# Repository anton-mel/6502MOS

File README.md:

# Simplified 6502 MOS

A simplified version of the MOS 6502 8-bit microprocessor with only a subset of its instructions. The 6502 is a classic CPU that powered some of the popular early systems such as the Apple II and NES.

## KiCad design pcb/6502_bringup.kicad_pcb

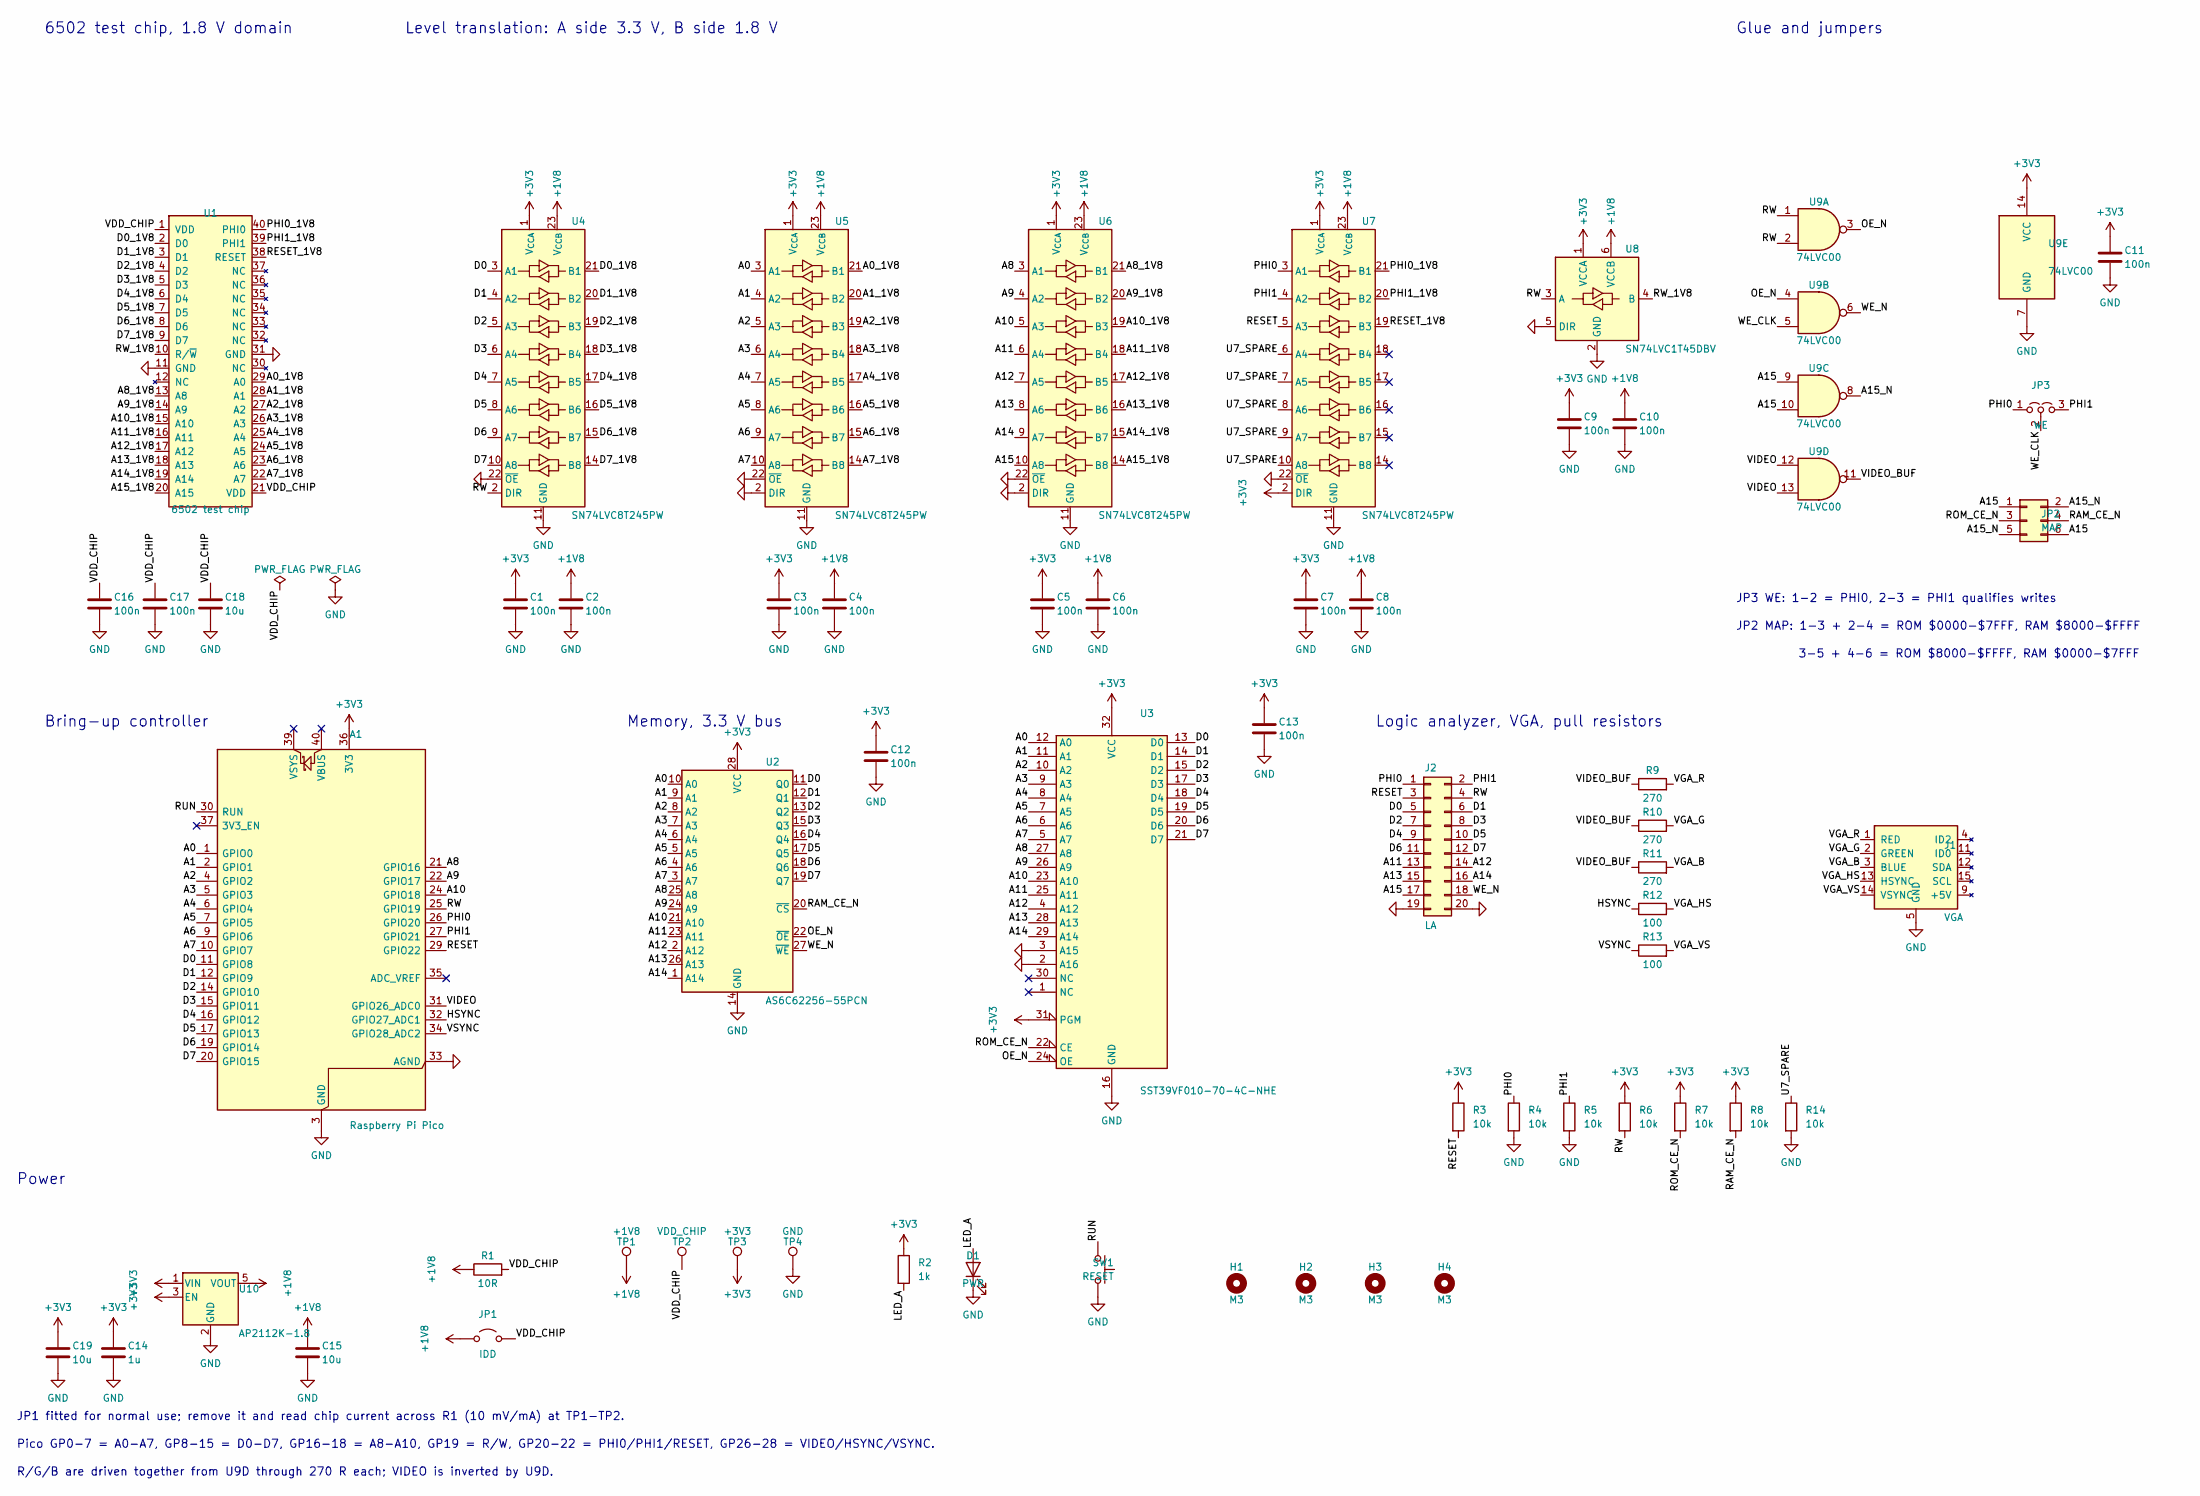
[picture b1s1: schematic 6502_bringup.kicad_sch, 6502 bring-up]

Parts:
A1: Raspberry Pi Pico; RaspberryPi_Pico_Common_THT; MPN SC0915
C1, C2, C3, C4, C5, C6, C7, C8, C9, C10, C11, C12, C13, C16, C17: 100n; C_0805_2012Metric
C14: 1u; C_0805_2012Metric
C15, C18, C19: 10u; C_0805_2012Metric
D1: PWR; LED_0805_2012Metric
H1, H2, H3, H4: M3; MountingHole_3.2mm_M3
J1: VGA; DSUB-15-HD_Socket_Horizontal_P2.29x1.90mm_EdgePinOffset3.03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
J2: LA; PinHeader_2x10_P2.54mm_Vertical
JP1: IDD; PinHeader_1x02_P2.54mm_Vertical
JP2: MAP; PinHeader_2x03_P2.54mm_Vertical
JP3: WE; PinHeader_1x03_P2.54mm_Vertical
R1: 10R; R_0805_2012Metric
R2: 1k; R_0805_2012Metric
R3, R4, R5, R6, R7, R8, R14: 10k; R_0805_2012Metric
R9, R10, R11: 270; R_0805_2012Metric
R12, R13: 100; R_0805_2012Metric
SW1: RESET; SW_PUSH_6mm
TP1: +1V8; TestPoint_Loop_D2.50mm_Drill1.0mm; MPN Keystone 5000
TP2: VDD_CHIP; TestPoint_Loop_D2.50mm_Drill1.0mm; MPN Keystone 5000
TP3: +3V3; TestPoint_Loop_D2.50mm_Drill1.0mm; MPN Keystone 5000
TP4: GND; TestPoint_Loop_D2.50mm_Drill1.0mm; MPN Keystone 5000
U1: 6502 test chip; ZIF-40_W15.24mm_3M_240-1280; MPN 3M 240-1280-00-0602J (socket)
U2: AS6C62256-55PCN; DIP-28_W15.24mm; MPN AS6C62256-55PCN
U3: SST39VF010-70-4C-NHE; PLCC-32_THT-Socket; MPN SST39VF010-70-4C-NHE
U4, U5, U6, U7: SN74LVC8T245PW; TSSOP-24_4.4x7.8mm_P0.65mm; MPN SN74LVC8T245PWR
U8: SN74LVC1T45DBV; SOT-23-6; MPN SN74LVC1T45DBVR
U9: 74LVC00; SOIC-14_3.9x8.7mm_P1.27mm; MPN SN74LVC00AD
U10: AP2112K-1.8; SOT-23-5; MPN AP2112K-1.8TRG1

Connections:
+1V8: C2.1, C4.1, C6.1, C8.1, C10.1, C15.1, JP1.1 (A), R1.1, TP1.1, U4.23 (V_{CCB}), U4.24 (V_{CCB}), U5.23 (V_{CCB}), U5.24 (V_{CCB}), U6.23 (V_{CCB}), U6.24 (V_{CCB}), U7.23 (V_{CCB}), U7.24 (V_{CCB}), U8.6 (VCCB), U10.5 (VOUT)
+3V3: A1.36 (3V3), C1.1, C3.1, C5.1, C7.1, C9.1, C11.1, C12.1, C13.1, C14.1, C19.1, R2.1, R3.1, R6.1, R7.1, R8.1, TP3.1, U2.28 (VCC), U3.31 (PGM), U3.32 (VCC), U4.1 (V_{CCA}), U5.1 (V_{CCA}), U6.1 (V_{CCA}), U7.1 (V_{CCA}), U7.2 (DIR), U8.1 (VCCA), U9.14 (VCC), U10.1 (VIN), U10.3 (EN)
/A0: A1.1 (GPIO0), U2.10 (A0), U3.12 (A0), U5.3 (A1)
/A0_1V8: U1.29 (A0), U5.21 (B1)
/A1: A1.2 (GPIO1), U2.9 (A1), U3.11 (A1), U5.4 (A2)
/A1_1V8: U1.28 (A1), U5.20 (B2)
/A2: A1.4 (GPIO2), U2.8 (A2), U3.10 (A2), U5.5 (A3)
/A2_1V8: U1.27 (A2), U5.19 (B3)
/A3: A1.5 (GPIO3), U2.7 (A3), U3.9 (A3), U5.6 (A4)
/A3_1V8: U1.26 (A3), U5.18 (B4)
/A4: A1.6 (GPIO4), U2.6 (A4), U3.8 (A4), U5.7 (A5)
/A4_1V8: U1.25 (A4), U5.17 (B5)
/A5: A1.7 (GPIO5), U2.5 (A5), U3.7 (A5), U5.8 (A6)
/A5_1V8: U1.24 (A5), U5.16 (B6)
/A6: A1.9 (GPIO6), U2.4 (A6), U3.6 (A6), U5.9 (A7)
/A6_1V8: U1.23 (A6), U5.15 (B7)
/A7: A1.10 (GPIO7), U2.3 (A7), U3.5 (A7), U5.10 (A8)
/A7_1V8: U1.22 (A7), U5.14 (B8)
/A8: A1.21 (GPIO16), U2.25 (A8), U3.27 (A8), U6.3 (A1)
/A8_1V8: U1.13 (A8), U6.21 (B1)
/A9: A1.22 (GPIO17), U2.24 (A9), U3.26 (A9), U6.4 (A2)
/A9_1V8: U1.14 (A9), U6.20 (B2)
/A10: A1.24 (GPIO18), U2.21 (A10), U3.23 (A10), U6.5 (A3)
/A10_1V8: U1.15 (A10), U6.19 (B3)
/A11: J2.13, U2.23 (A11), U3.25 (A11), U6.6 (A4)
/A11_1V8: U1.16 (A11), U6.18 (B4)
/A12: J2.14, U2.2 (A12), U3.4 (A12), U6.7 (A5)
/A12_1V8: U1.17 (A12), U6.17 (B5)
/A13: J2.15, U2.26 (A13), U3.28 (A13), U6.8 (A6)
/A13_1V8: U1.18 (A13), U6.16 (B6)
/A14: J2.16, U2.1 (A14), U3.29 (A14), U6.9 (A7)
/A14_1V8: U1.19 (A14), U6.15 (B7)
/A15: J2.17, JP2.1, JP2.6, U6.10 (A8), U9.9, U9.10
/A15_1V8: U1.20 (A15), U6.14 (B8)
/A15_N: JP2.2, JP2.5, U9.8
/D0: A1.11 (GPIO8), J2.5, U2.11 (Q0), U3.13 (D0), U4.3 (A1)
/D0_1V8: U1.2 (D0), U4.21 (B1)
/D1: A1.12 (GPIO9), J2.6, U2.12 (Q1), U3.14 (D1), U4.4 (A2)
/D1_1V8: U1.3 (D1), U4.20 (B2)
/D2: A1.14 (GPIO10), J2.7, U2.13 (Q2), U3.15 (D2), U4.5 (A3)
/D2_1V8: U1.4 (D2), U4.19 (B3)
/D3: A1.15 (GPIO11), J2.8, U2.15 (Q3), U3.17 (D3), U4.6 (A4)
/D3_1V8: U1.5 (D3), U4.18 (B4)
/D4: A1.16 (GPIO12), J2.9, U2.16 (Q4), U3.18 (D4), U4.7 (A5)
/D4_1V8: U1.6 (D4), U4.17 (B5)
/D5: A1.17 (GPIO13), J2.10, U2.17 (Q5), U3.19 (D5), U4.8 (A6)
/D5_1V8: U1.7 (D5), U4.16 (B6)
/D6: A1.19 (GPIO14), J2.11, U2.18 (Q6), U3.20 (D6), U4.9 (A7)
/D6_1V8: U1.8 (D6), U4.15 (B7)
/D7: A1.20 (GPIO15), J2.12, U2.19 (Q7), U3.21 (D7), U4.10 (A8)
/D7_1V8: U1.9 (D7), U4.14 (B8)
/HSYNC: A1.32 (GPIO27_ADC1), R12.1
/LED_A: D1.2 (A), R2.2
/OE_N: U2.22 (~OE), U3.24 (OE), U9.3, U9.4
/PHI0: A1.26 (GPIO20), J2.1, JP3.1 (A), R4.1, U7.3 (A1)
/PHI0_1V8: U1.40 (PHI0), U7.21 (B1)
/PHI1: A1.27 (GPIO21), J2.2, JP3.3 (B), R5.1, U7.4 (A2)
/PHI1_1V8: U1.39 (PHI1), U7.20 (B2)
/RAM_CE_N: JP2.4, R8.2, U2.20 (~CS)
/RESET: A1.29 (GPIO22), J2.3, R3.2, U7.5 (A3)
/RESET_1V8: U1.38 (RESET), U7.19 (B3)
/ROM_CE_N: JP2.3, R7.2, U3.22 (CE)
/RUN: A1.30 (RUN), SW1.1
/RW: A1.25 (GPIO19), J2.4, R6.2, U4.2 (DIR), U8.3 (A), U9.1, U9.2
/RW_1V8: U1.10 (R/~W), U8.4 (B)
/U7_SPARE: R14.1, U7.6 (A4), U7.7 (A5), U7.8 (A6), U7.9 (A7), U7.10 (A8)
/VDD_CHIP: C16.1, C17.1, C18.1, JP1.2 (B), R1.2, TP2.1, U1.1 (VDD), U1.21 (VDD)
/VGA_B: J1.3 (BLUE), R11.2
/VGA_G: J1.2 (GREEN), R10.2
/VGA_HS: J1.13 (HSYNC), R12.2
/VGA_R: J1.1 (RED), R9.2
/VGA_VS: J1.14 (VSYNC), R13.2
/VIDEO: A1.31 (GPIO26_ADC0), U9.12, U9.13
/VIDEO_BUF: R9.1, R10.1, R11.1, U9.11
/VSYNC: A1.34 (GPIO28_ADC2), R13.1
/WE_CLK: JP3.2 (C), U9.5
/WE_N: J2.18, U2.27 (~WE), U9.6
GND: A1.3 (GND), A1.8 (GND), A1.13 (GND), A1.18 (GND), A1.23 (GND), A1.28 (GND), A1.33 (AGND), A1.38 (GND), C1.2, C2.2, C3.2, C4.2, C5.2, C6.2, C7.2, C8.2, C9.2, C10.2, C11.2, C12.2, C13.2, C14.2, C15.2, C16.2, C17.2, C18.2, C19.2, D1.1 (K), J1.5 (GND), J1.6 (GND), J1.7 (GND), J1.8 (GND), J1.10 (GND), J1.SH (GND), J2.19, J2.20, R4.2, R5.2, R14.2, SW1.2, TP4.1, U1.11 (GND), U1.31 (GND), U2.14 (GND), U3.2 (A16), U3.3 (A15), U3.16 (GND), U4.11 (GND), U4.12 (GND), U4.13 (GND), U4.22 (~OE), U5.2 (DIR), U5.11 (GND), U5.12 (GND), U5.13 (GND), U5.22 (~OE), U6.2 (DIR), U6.11 (GND), U6.12 (GND), U6.13 (GND), U6.22 (~OE), U7.11 (GND), U7.12 (GND), U7.13 (GND), U7.22 (~OE), U8.2 (GND), U8.5 (DIR), U9.7 (GND), U10.2 (GND)

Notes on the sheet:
6502 test chip, 1.8 V domain
Level translation: A side 3.3 V, B side 1.8 V
Glue and jumpers
Bring-up controller
Memory, 3.3 V bus
Logic analyzer, VGA, pull resistors
Power
JP3 WE: 1-2 = PHI0, 2-3 = PHI1 qualifies writes
JP2 MAP: 1-3 + 2-4 = ROM $0000-$7FFF, RAM $8000-$FFFF
3-5 + 4-6 = ROM $8000-$FFFF, RAM $0000-$7FFF
JP1 fitted for normal use; remove it and read chip current across R1 (10 mV/mA) at TP1-TP2.
Pico GP0-7 = A0-A7, GP8-15 = D0-D7, GP16-18 = A8-A10, GP19 = R/W, GP20-22 = PHI0/PHI1/RESET, GP26-28 = VIDEO/HSYNC/VSYNC.
R/G/B are driven together from U9D through 270 R each; VIDEO is inverted by U9D.

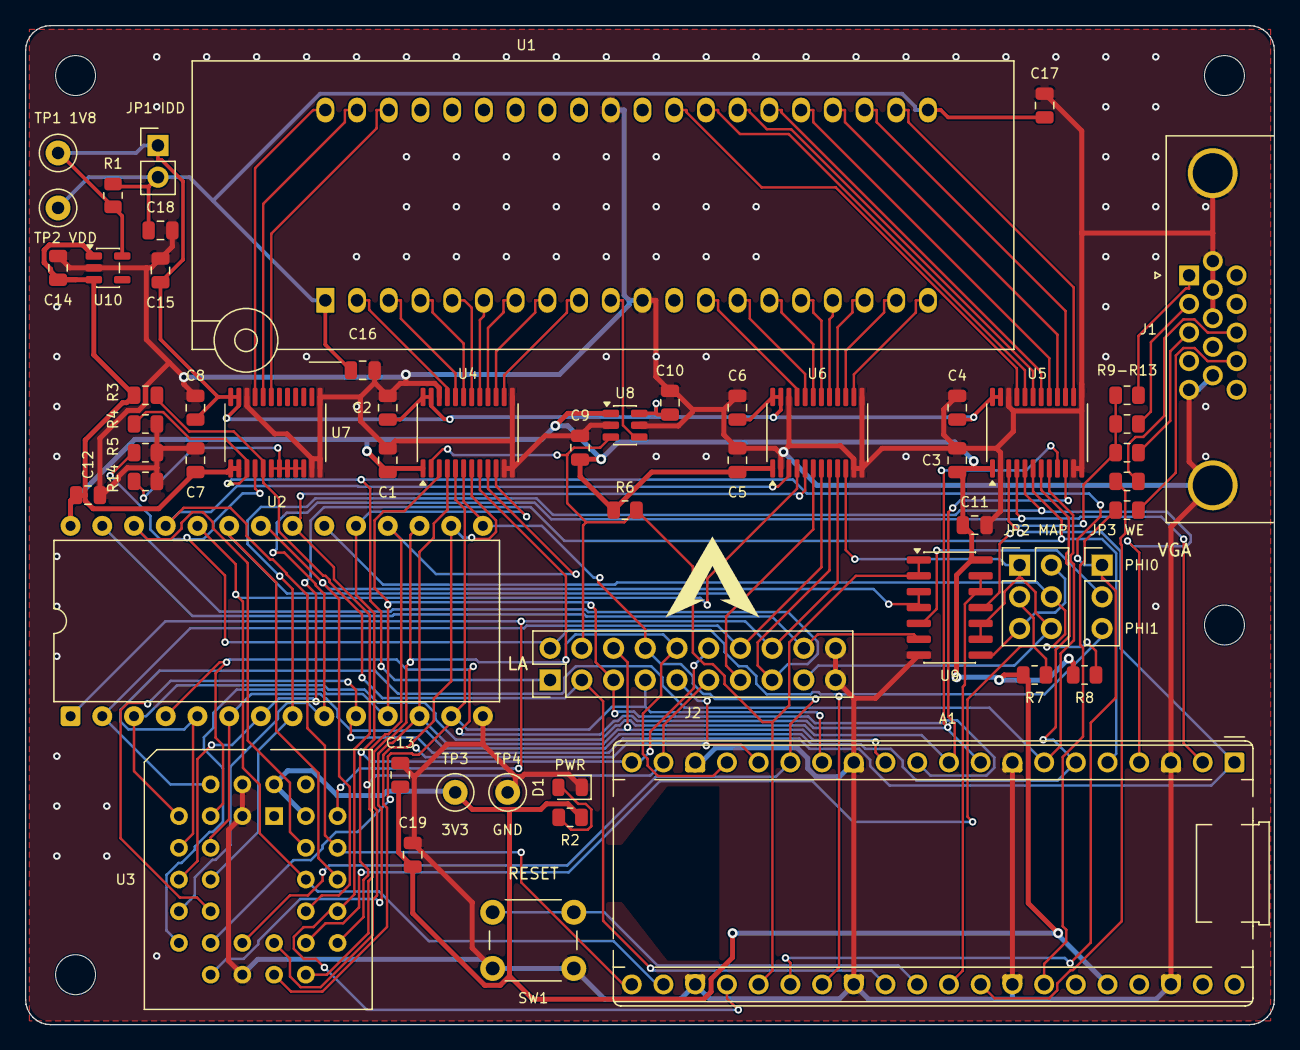
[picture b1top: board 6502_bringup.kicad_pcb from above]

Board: 2 copper layers, 100.0 x 80.0 mm, 59 parts (0 on the bottom side), 78 nets.
